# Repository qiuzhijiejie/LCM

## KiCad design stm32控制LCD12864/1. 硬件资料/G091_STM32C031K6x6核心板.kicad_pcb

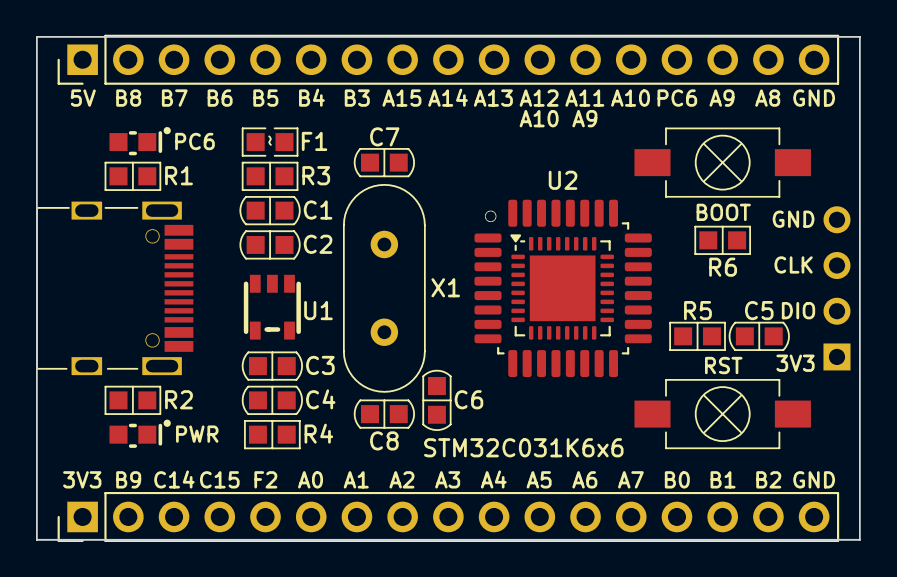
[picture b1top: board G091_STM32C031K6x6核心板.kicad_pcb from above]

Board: 2 copper layers, 45.7 x 27.9 mm, 26 parts (0 on the bottom side), 36 nets, no tracks yet.

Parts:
C1, C3: 10uF; C0603
C2, C4, C5, C6: 100nF; C0603
C7, C8: 22pF; C0603
F1: 6V/0.85A; Fuse-0603
LED1, LED2: LED0603
P1: Header1X4; Header 1X4P With Angle Pin
P2: USB_C_Plug; USB-TYPEC-12PIN
P3, P4: Header1x17P; Header 1X17P
R1, R2: 4.7k; R0603
R3, R4: 5.1k; R0603
R5, R6: 10k; R0603
S1, S2: SW-PB
U1: ME6211C33M5G; SOT-23-5
U2: STM32C031K6x6; LQFP32-0.8mm
X1: 8MHZ; Crystal-HC49S

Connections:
+3V3: C3.2, C4.2, C6.2, P1.1, P3.1, R1.2, R2.2, R5.2, S1.2, U1.5 (VOUT), U2.4 (VDD)
/OSC_IN: C7.1, P3.3, U2.2 (PC14), X1.2
/OSC_OUT: C8.1, P3.4, U2.3 (PC15), X1.1
/PA0: P3.6, U2.7 (PA0)
/PA1: P3.7, U2.8 (PA1)
/PA2: P3.8, U2.9 (PA2)
/PA4: P3.10, U2.11 (PA4)
/PA5: P3.11, U2.12 (PA5)
/PA6: P3.12, U2.13 (PA6)
/PA7: P3.13, U2.14 (PA7)
/PA8: P4.16, U2.18 (PA8)
/PA9: P4.15, U2.19 (PA9/NC)
/PA10: P4.13, U2.21 (PA10/NC)
/PA11/PA9: P4.12, U2.22 (PA11/PA9)
/PA12/PA10: P4.11, U2.23 (PA12/PA10)
/PA15: P4.8, U2.26 (PA15)
/PB0: P3.14, U2.15 (PB0)
/PB1: P3.15, U2.16 (PB1)
/PB2: P3.16, U2.17 (PB2)
/PB3: P4.7, U2.27 (PB3)
/PB4: P4.6, U2.28 (PB4)
/PB5: P4.5, U2.29 (PB5)
/PB6: P4.4, U2.30 (PB6)
/PB7: P4.3, U2.31 (PB7)
/PB8: P4.2, U2.32 (PB8)
/PB9: P3.2, U2.1 (PB9)
/PC6: LED1.1, P4.14, U2.20 (PC6)
/RST: C5.2, P3.5, R5.1, S2.2, U2.6 (PF2)
/SWCLK: P1.3, P4.9, R6.1, S1.1, U2.25 (PA14)
/SWDIO: P1.2, P4.10, U2.24 (PA13)
GND: C1.1, C2.1, C3.1, C4.1, C5.1, C6.1, C7.2, C8.2, LED2.1, P1.4, P2.1 (GND), P2.12 (GND), P3.17, P4.17, R3.1, R4.1, R6.2, S2.1, U1.2 (VSS), U2.5 (VSS), U2.33 (VSS)
unnamed: F1.2, P2.2 (VCC), P2.11 (VCC)
unnamed: LED1.2, R1.1
unnamed: LED2.2, R2.1
unnamed: P2.3 (NC), R3.2
unnamed: P2.10 (NC), R4.2

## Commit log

2024-10-14 lcd屏幕
2024-10-14 lcd屏幕代码
2024-10-15 Code
2024-10-17 修改little error
